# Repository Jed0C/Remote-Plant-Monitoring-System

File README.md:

# Remote Plant Monitoring System

## Overview
The Remote Plant Monitoring System is designed to monitor the environmental conditions of plants remotely. It collects real-time data on temperature, humidity, and GPS location, and transmits this data using LoRa (Long Range) communication.

The system uses the ESP32 microcontroller, interfacing with the AM2315C I2C Temperature/Humidity Sensor, MTK3339 GPS Module, and RA-02 LoRa Module. This system is suitable for agricultural applications, where remote monitoring is essential to ensure optimal plant conditions.

## Features
- Temperature and Humidity Monitoring: Uses the AM2315C I2C sensor to measure temperature and humidity in the plant's environment.
- GPS Location: The MTK3339 GPS Module provides GPS coordinates, allowing for the tracking of plant location.
- Long-range Communication: The RA-02 LoRa Module enables communication over long distances (up to several kilometers), sending data to a base station or server.
- Low Power Consumption: Powered by a battery circuit, the system is designed for low power operation with deep sleep functionality for extended use in the field.
- Wireless Data Transmission: All data is transmitted wirelessly, making the system ideal for remote or hard-to-reach locations.
## Components Used
- ESP32-WROOM-32 Microcontroller: A versatile microcontroller with Wi-Fi and Bluetooth capabilities, acting as the central control unit.
- AM2315C Temperature/Humidity Sensor: An I2C-based sensor that measures temperature and humidity in the surrounding environment.
- MTK3339 GPS Module: A GPS module for acquiring the geographical location (latitude and longitude) of the monitoring system.
- RA-02 LoRa Module: A long-range wireless communication module using LoRaWAN technology, transmitting sensor data over great distances.

- Battery Circuit: A power supply system to power the entire setup, including charging and voltage regulation.

## Installation
### Software Setup

Install Libraries:

- AM2315C Sensor: Install the Adafruit AHTx0 Library.
- GPS Module: Install TinyGPSPlus Library.
- LoRa Communication: Install the LoRa library.
In Arduino IDE, go to Sketch > Include Library > Manage Libraries and search for the necessary libraries to install.

## Usage
The ESP32 will initialize the sensor and GPS module.
The system will periodically collect humidity, and GPS coordinates data from the AM2315C sensor and the MTK3339 GPS module.
The collected data will be transmitted via the RA-02 LoRa Module to a receiver base station or a cloud server.
The data can be visualized or logged at the receiving end, such as an ESP32 with LoRa module or a cloud-based platform.
- Power Management
The system is designed to run on a solar cell and battery ,and uses deep sleep modes on the ESP32 to reduce power consumption during idle periods.

## Contributing
Feel free to fork this project and contribute to improvements or bug fixes. If you have suggestions or questions, open an issue on the repository.

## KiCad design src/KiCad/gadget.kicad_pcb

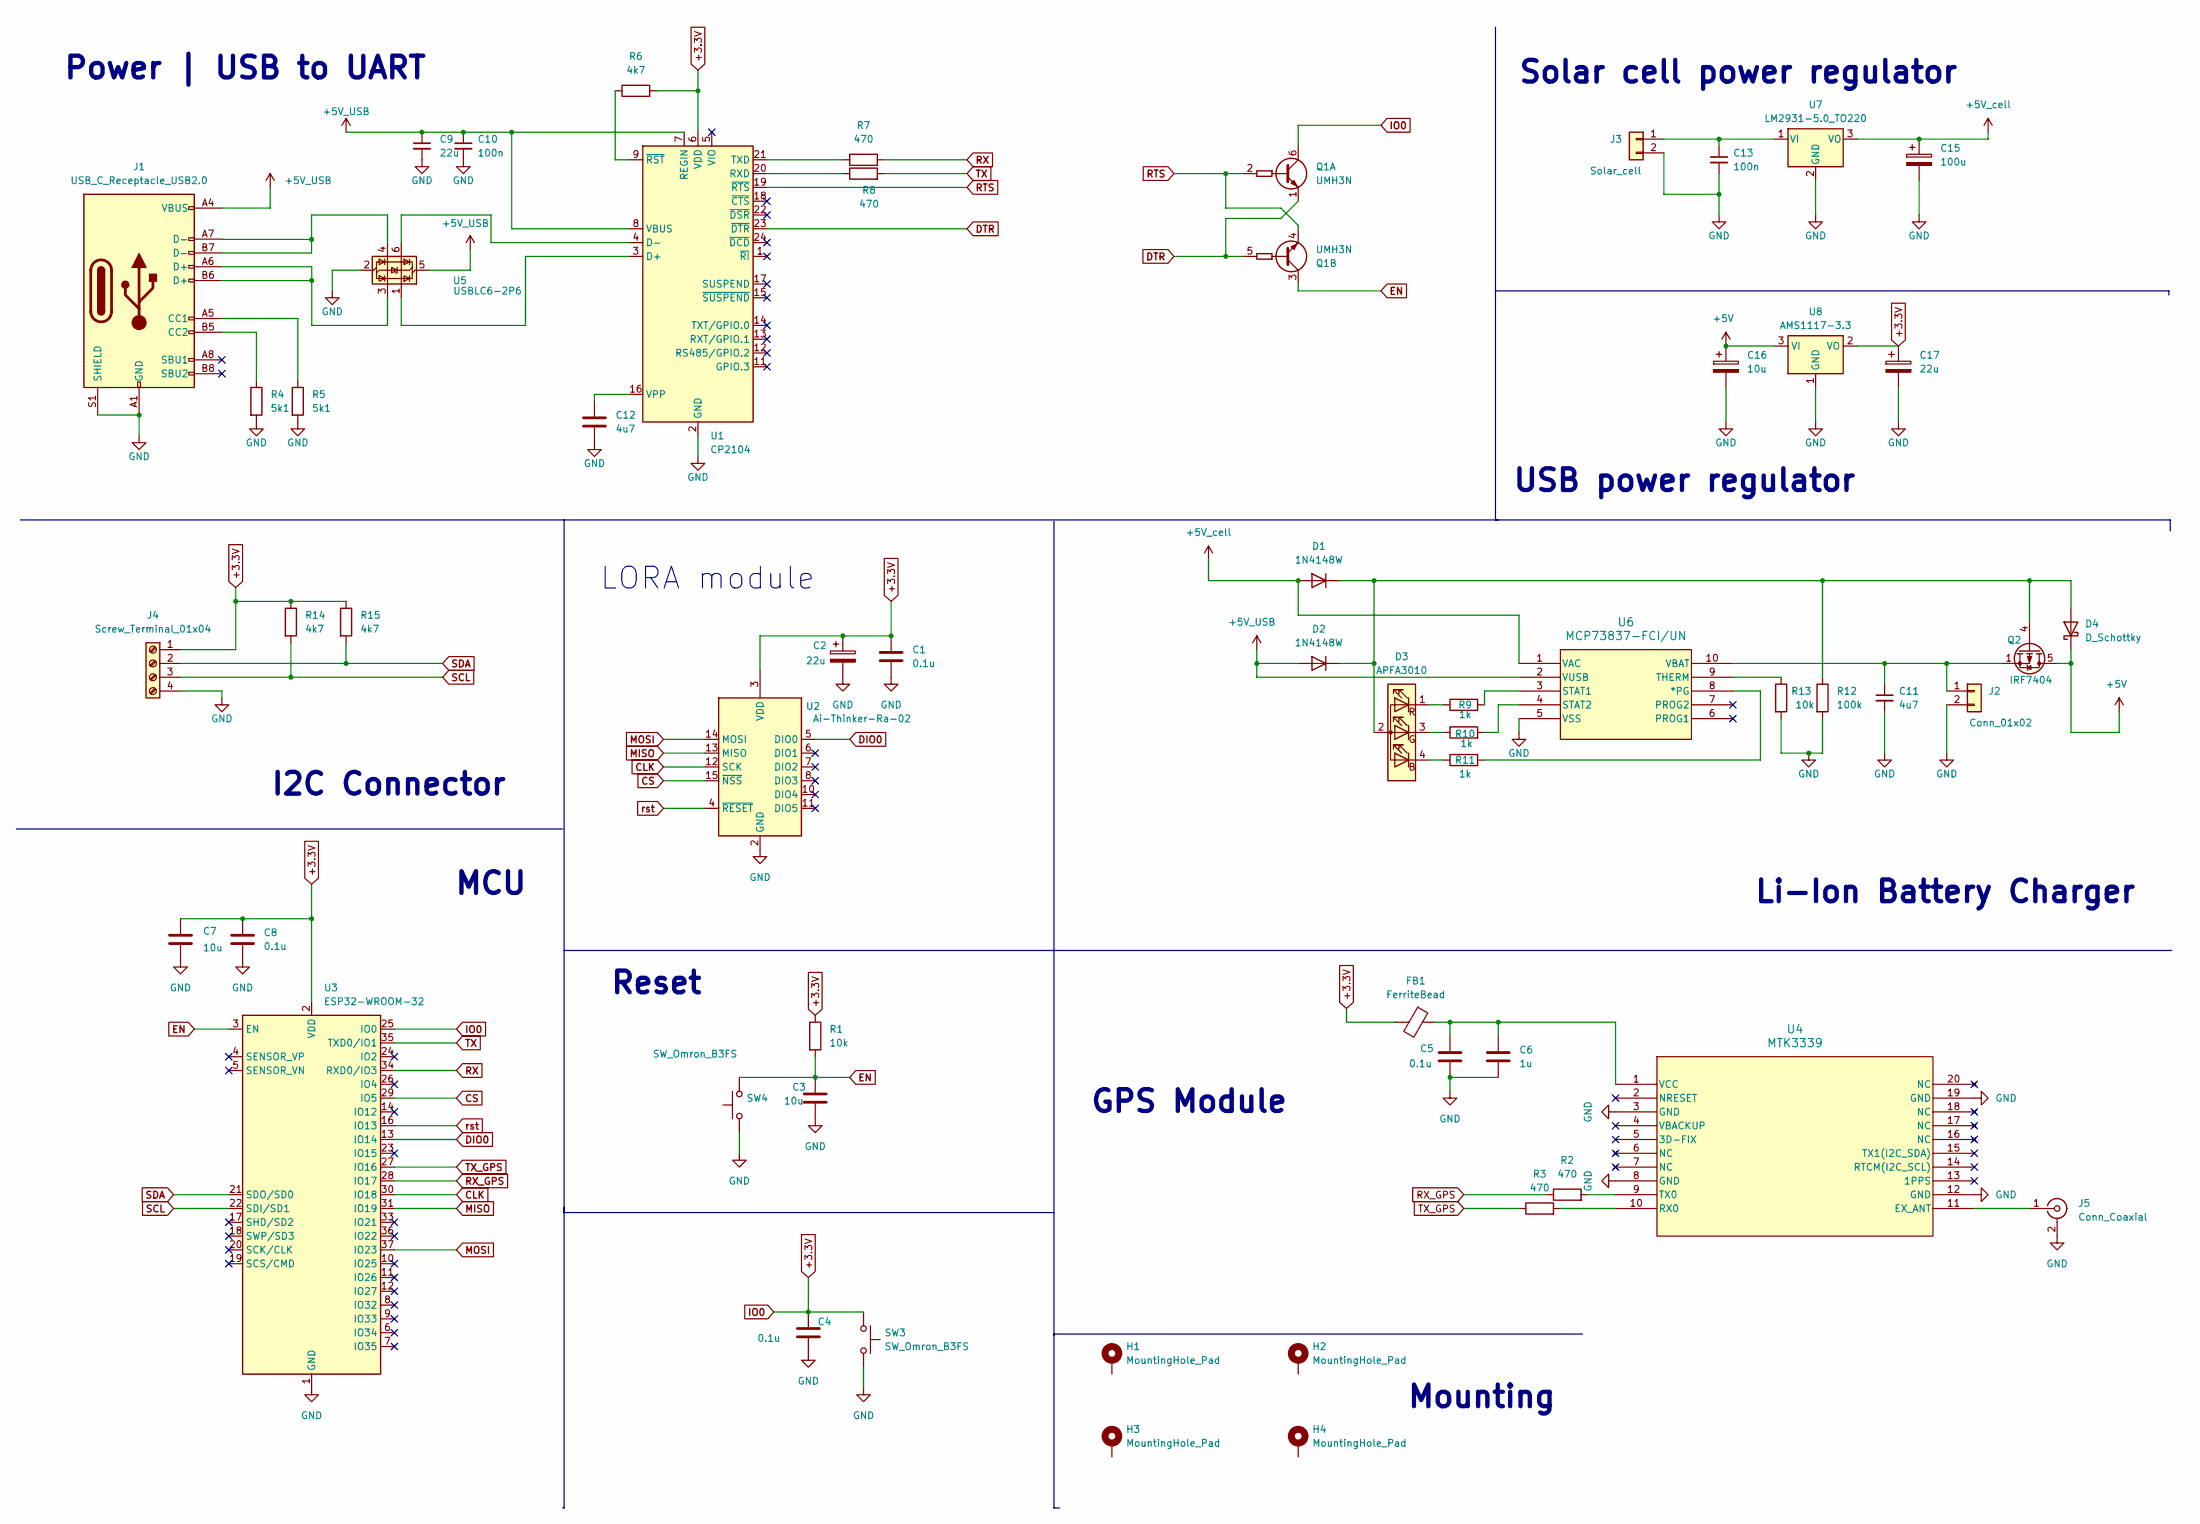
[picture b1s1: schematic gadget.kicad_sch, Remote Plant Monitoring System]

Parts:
C1, C4, C5, C8: 0.1u; C_0805_2012Metric_Pad1.18x1.45mm_HandSolder
C2, C9, C17: 22u; C_0402_1005Metric_Pad0.74x0.62mm_HandSolder
C3, C7, C16: 10u; C_0402_1005Metric_Pad0.74x0.62mm_HandSolder
C6: 1u; C_0402_1005Metric_Pad0.74x0.62mm_HandSolder
C10, C13: 100n; C_0402_1005Metric_Pad0.74x0.62mm_HandSolder
C11, C12: 4u7; C_0402_1005Metric_Pad0.74x0.62mm_HandSolder
C15: 100u; C_0805_2012Metric_Pad1.18x1.45mm_HandSolder
D1, D2: 1N4148W; D_SOD-123
D3: APFA3010; LED_Kingbright_APFA3010_3x1.5mm_Horizontal
D4: D_Schottky; D_0201_0603Metric
FB1: FerriteBead; L_0805_2012Metric
H1, H2, H3, H4: MountingHole_Pad; MountingHole_2.2mm_M2_DIN965_Pad
J1: USB_C_Receptacle_USB2.0; USB_C_Receptacle_GCT_USB4085
J2: Conn_01x02; JST_EH_B2B-EH-A_1x02_P2.50mm_Vertical
J3: Solar_cell; JST_EH_B2B-EH-A_1x02_P2.50mm_Vertical
J4: Screw_Terminal_01x04; TerminalBlock_Phoenix_MKDS-1,5-4-5.08_1x04_P5.08mm_Horizont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
J5: Conn_Coaxial; U.FL_Hirose_U.FL-R-SMT-1_Vertical
Q1: UMH3N; SOT-363_SC-70-6
Q2: IRF7404
R1, R13: 10k; R_0805_2012Metric_Pad1.20x1.40mm_HandSolder
R2, R3, R7, R8: 470; R_0603_1608Metric_Pad0.98x0.95mm_HandSolder
R4, R5: 5k1; R_0603_1608Metric_Pad0.98x0.95mm_HandSolder
R6, R14, R15: 4k7; R_0603_1608Metric_Pad0.98x0.95mm_HandSolder
R9, R10, R11: 1k; R_0603_1608Metric_Pad0.98x0.95mm_HandSolder
R12: 100k; R_0805_2012Metric_Pad1.20x1.40mm_HandSolder
SW3, SW4: SW_Omron_B3FS; SW_SPST_Omron_B3FS-100xP
U1: CP2104; QFN-24-1EP_4x4mm_P0.5mm_EP2.6x2.6mm
U2: Ai-Thinker-Ra-02; Ai-Thinker-Ra-01-LoRa
U3: ESP32-WROOM-32
U4: MTK3339; PA1616S_ADA
U5: USBLC6-2P6; SOT-666
U6: MCP73837-FCI/UN; MSOP10_MC_MCH
U7: LM2931-5.0_TO220; TO-220-3_Vertical
U8: AMS1117-3.3; SOT-223-3_TabPin2

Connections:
+3.3V: C1.1, C2.1, C4.1, C7.1, C8.1, C17.1, FB1.2, J4.1, Q1.6 (C1), R1.1, R6.2, R14.1, R15.1, SW3.1, U1.6 (VDD), U2.3 (VDD), U3.2 (VDD), U3.25 (IO0), U8.2 (VO)
+5V: C16.1, D4.1 (K), Q2.5 (D), Q2.6 (D), Q2.7 (D), Q2.8 (D), U8.3 (VI)
+5V_USB: C9.1, C10.1, D2.2 (A), J1.A4 (VBUS), J1.A9 (VBUS), J1.B4 (VBUS), J1.B9 (VBUS), U1.7 (REGIN), U1.8 (VBUS), U5.5 (VBUS), U6.2 (VUSB)
+5V_cell: C15.1, D1.2 (A), U6.1 (VAC), U7.3 (VO)
CLK: U2.12 (SCK), U3.30 (IO18)
CS: U2.15 (~NSS), U3.29 (IO5)
DIO0: U2.5 (DIO0), U3.13 (IO14)
DTR: Q1.1 (E1), Q1.5 (B2), U1.23 (~DTR)
EN: C3.1, Q1.3 (C2), R1.2, SW4.2, U3.3 (EN)
GND: C1.2, C2.2, C3.2, C4.2, C5.2, C6.2, C7.2, C8.2, C9.2, C10.2, C11.2, C12.2, C13.2, C15.2, C16.2, C17.2, J1.A1 (GND), J1.A12 (GND), J1.B1 (GND), J1.B12 (GND), J1.S1 (SHIELD), J2.2, J3.2, J4.4, J5.2 (Ext), R4.2, R5.2, R12.2, R13.2, SW3.2, SW4.1, U1.2 (GND), U1.25 (GND), U2.1 (GND), U2.2 (GND), U2.9 (GND), U2.16 (GND), U3.1 (GND), U3.15 (GND), U3.38 (GND), U3.39 (GND), U4.3 (GND), U4.8 (GND), U4.12 (GND), U4.19 (GND), U5.2 (GND), U6.5 (VSS), U7.2 (GND), U8.1 (GND)
MISO: U2.13 (MISO), U3.31 (IO19)
MOSI: U2.14 (MOSI), U3.37 (IO23)
unnamed: D1.1 (K), D2.1 (K), D3.2 (A), D4.2 (A), Q2.4 (G), R12.1
unnamed: D3.4 (B), R11.1
unnamed: D3.3 (G), R10.1
unnamed: D3.1 (R), R9.1
unnamed: J1.A5 (CC1), R5.1
unnamed: J1.B5 (CC2), R4.1
unnamed: J1.A6 (D+), J1.B6 (D+), U5.3 (I/O2)
unnamed: J1.A7 (D-), J1.B7 (D-), U5.4 (I/O2)
unnamed: C11.1, J2.1, Q2.1 (S), Q2.2 (S), Q2.3 (S), U6.10 (VBAT)
unnamed: C13.1, J3.1, U7.1 (VI)
unnamed: J5.1 (In), U4.11 (EX_ANT)
unnamed: U1.3 (D+), U5.1 (I/O1)
unnamed: U1.4 (D-), U5.6 (I/O1)
unnamed: R8.1, U1.20 (RXD)
unnamed: R7.1, U1.21 (TXD)
unnamed: C12.1, U1.16 (VPP)
unnamed: R6.1, U1.9 (~RST)
unnamed: R3.2, U4.10 (RX0)
unnamed: R2.2, U4.9 (TX0)
unnamed: C5.1, C6.1, FB1.1, U4.1 (VCC)
unnamed: R11.2, U6.8 (*PG)
unnamed: R9.2, U6.3 (STAT1)
unnamed: R10.2, U6.4 (STAT2)
unnamed: R13.1, U6.9 (THERM)
RTS: Q1.2 (B1), Q1.4 (E2), U1.19 (~RTS)
RX: R7.2, U3.34 (RXD0/IO3)
RX_GPS: R2.1, U3.28 (IO17)
SCL: J4.3, R14.2, U3.22 (SDI/SD1)
SDA: J4.2, R15.2, U3.21 (SDO/SD0)
TX: R8.2, U3.35 (TXD0/IO1)
TX_GPS: R3.1, U3.27 (IO16)
rst: U2.4 (~RESET), U3.16 (IO13)

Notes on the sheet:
I2C Connector
Reset
MCU
Power | USB to UART
Mounting
GPS Module
Li-Ion Battery Charger
LORA module
Solar cell power regulator
USB power regulator

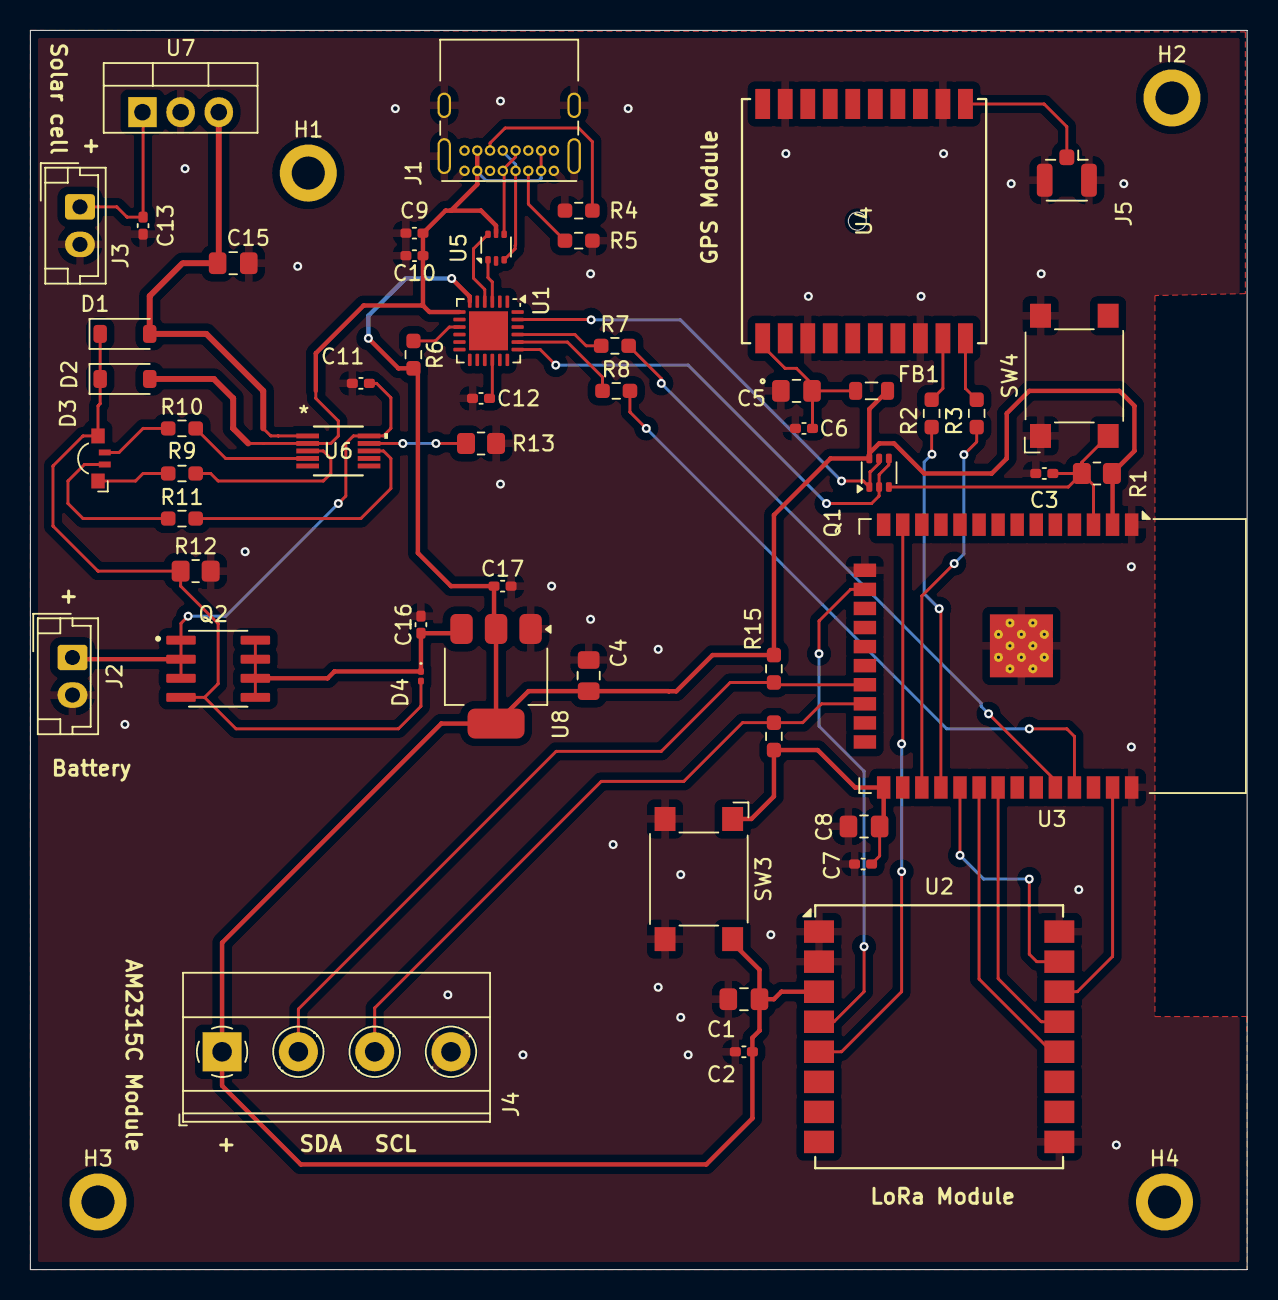
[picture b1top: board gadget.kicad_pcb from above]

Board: 2 copper layers, 81.0 x 82.5 mm, 57 parts (0 on the bottom side), 44 nets.

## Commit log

2025-01-28 project
